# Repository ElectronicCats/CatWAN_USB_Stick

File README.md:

# CatWAN USB Stick
<p align="center">
    
</p>

<p align=center><b>Where to buy and learn more</b></p>
<p align=center>

</p>

<p align=center>
  
</p>

Are you interested in learning how LoRa works at the package level? Debugging your own LoRa hardware and trying to detect where something is wrong? Or maybe you're writing a custom application for your Internet of Things (IoT) network with LoraWAN? We have the perfect tool for you!

This CatWAN USB Stick is programmed with a special firmware image that makes it an easy-to-use LoRa sniffer. You can passively capture the data exchanges between two LoRa devices, capturing with our "LoRa Sniffer" the open-source network analysis tool that we have created to use together.

This device can work in networks LoRaWAN compatible with classes A, B, and C, although currently we do not have a firmware for this way of working, the CatWAN firmware is completely open source and you can find it in our repository along with the schematic. If you want to reprogram this device you can do it through Arduino IDE and its USB port or if you do not have to use a J-Link. ATMEL-ICE or a DIY SWD programmer

This device has a SAMD21 ARM Cortex microcontroller at 48Mhz with native USB 2.1, with 256Kb for programming, compatible with Arduino and Circuit Python.

Check our repository for more details and software downloads!

### Main characteristics

- Works with any PC, Raspberry Pi or BeagleBone, even a smartphone or tablet
- Supports packet mode LoRa® (package mode) or LoRaWAN ™ Class A, B and C
- Compatible with The Things Network and other LoRaWAN networks
- Based on the RFM95
- RX LED as reception indicator, programmable by the user
- Easy reprogramming compatible with Arduino and Circuit Python
- Compatible with the [App LoRa Sniffer](https://github.com/ElectronicCats/LoRa_Sniffer)
- Open Source

### Specifications

- Connectivity: USB 2.1
- Power Consumption: 140 ma typical TX, 20 ma idle (with power LED)
- Receiver Sensitivity: down to -146 dBm
- TX Power: adjustable up to +18.5 dBm
- Range: up to 15 km coverage in suburban and up to 5 km coverage in urban areas

### Pin connections

|Arduino |   Port    |   RFM Function|
|--------|-----------|---------------|
|0       |   PORTA4  |   DIO0   |
|1       |   PORTA23 |   DIO1   |
|2       |   PORTA27 |   DIO2   |
|13      |   PORTA14 |   LED    |
|15      |   PORTA15 |   DIO5   |
|17      |   PORTA22 |   MISO   |
|18      |   PORTA18 |   MOSI   |
|19      |   PORTA19 |   SCK    |
|20      |   PORTA17 |   SS     |

## How to contribute 
 Contributions are welcome! 

Please read the document  [**Contribution Manual**](https://github.com/ElectronicCats/electroniccats-cla/blob/main/electroniccats-contribution-manual.md)  which will show you how to contribute your changes to the project.

✨ Thanks to all our [contributors](https://github.com/ElectronicCats/CatWAN_USB_Stick/graphs/contributors)! ✨

See  [**_Electronic Cats CLA_**](https://github.com/ElectronicCats/electroniccats-cla/blob/main/electroniccats-cla.md) for more information.

See the [**community code of conduct**](https://github.com/ElectronicCats/electroniccats-cla/blob/main/electroniccats-community-code-of-conduct.md)   for a vision of the community we want to build and what we expect from it.

### Maintainer

Electronic Cats invests time and resources in providing this open-source design design, please support Electronic Cats and open-source hardware by purchasing products from Electronic Cats!

## Open Source certified.
<p align="center">
    <a href="https://www.oshwa.org/cert">
        
        <br>
        <strong>[OSHW] MX000006 | Certified open source hardware |</strong>
    </a>
</p>

Designed by Electronic Cats.

Firmware released under an GNU AGPL v3.0 license. See the LICENSE file for more information.

Hardware released under an CERN Open Hardware Licence v1.2. See the LICENSE_HARDWARE file for more information.

Electronic Cats is a registered trademark, please do not use if you sell these PCBs.

27 May 2019

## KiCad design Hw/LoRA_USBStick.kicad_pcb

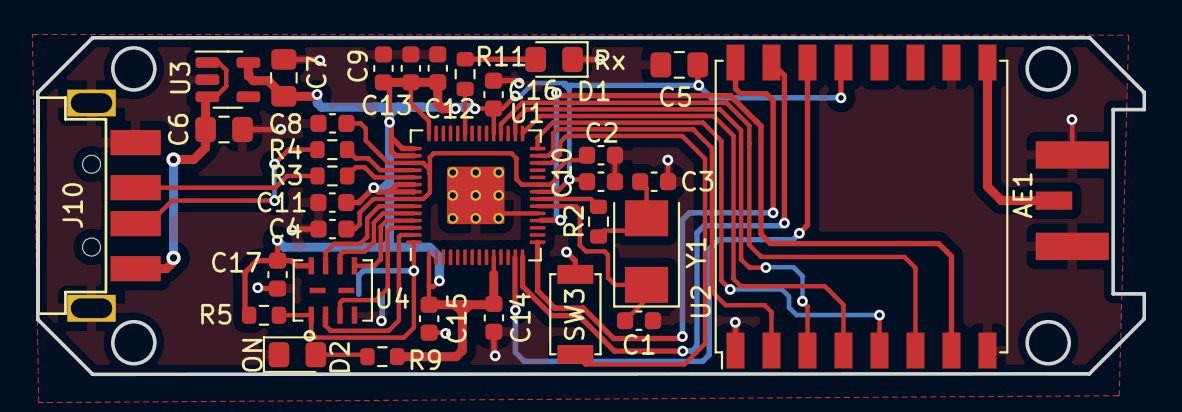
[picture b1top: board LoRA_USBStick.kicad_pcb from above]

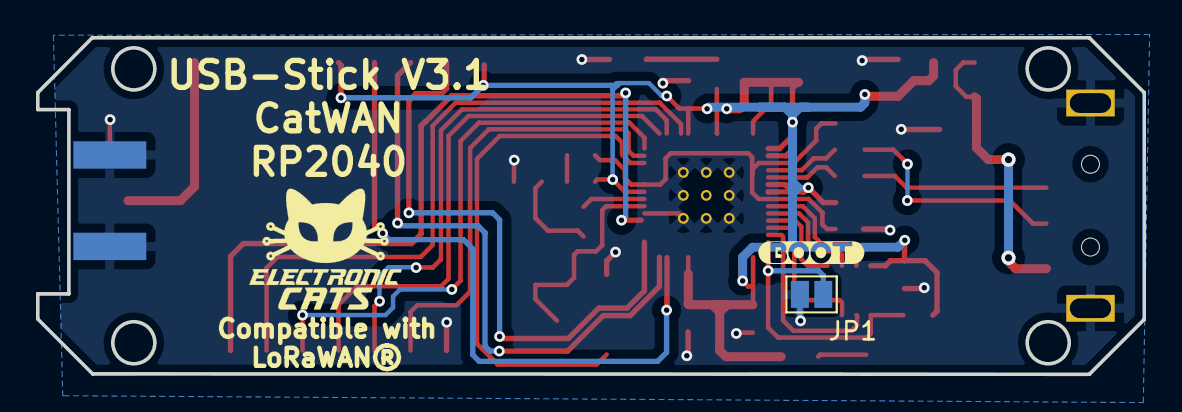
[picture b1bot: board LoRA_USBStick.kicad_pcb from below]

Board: 2 copper layers, 61.5 x 18.7 mm, 35 parts (2 on the bottom side), 31 nets.

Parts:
AE1: Antenna_Shield; SMA_EDGE
C1, C3: 27pF; C_0603_1608Metric
C2, C9: 1uF; C_0603_1608Metric
C4, C8, C10, C11, C12, C13, C14, C15, C16, C17: 0.1uF; C_0603_1608Metric
C5: 0.1uF; C_0805_2012Metric_Pad1.15x1.40mm_HandSolder
C6, C7: 10uF; C_0805_2012Metric_Pad1.15x1.40mm_HandSolder
D1: Rx; LED_0805_2012Metric_Pad1.15x1.40mm_HandSolder
D2: ON; LED_0805_2012Metric_Pad1.15x1.40mm_HandSolder
J10: USB_B; C46394
JP1: BOOT; SolderJumper-2_P1.3mm_Open_Pad1.0x1.5mm
R2: 1K; R_0603_1608Metric
R3, R4: 27; R_0603_1608Metric
R5: 10K; R_0603_1608Metric
R9, R11: 120R; R_0603_1608Metric
SW3: RST; C455281
U1: RP2040; RP2040-QFN-56
U2: RFM95W-868S2; HOPERF_RFM9XW_SMD
U3: AP2112K-3.3; SOT-23-5
U4: W25Q16JV; W25Q16JVUUIQ
Y1: 12Mhz; Crystal_SMD_5032-2Pin_5.0x3.2mm
kibuzzard-62D459CC: G***; kibuzzard-62D459CC

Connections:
+1V2: C2.1, C4.1, C8.1, U1.23 (DVDD), U1.45 (VREG_VOUT), U1.50 (DVDD)
+3V3: C5.1, C7.1, C9.1, C10.1, C11.1, C12.1, C13.1, C14.1, C15.1, C16.1, C17.1, R5.1, R9.1, U1.1 (IOVDD), U1.10 (IOVDD), U1.22 (IOVDD), U1.33 (IOVDD), U1.42 (IOVDD), U1.43 (ADC_AVDD), U1.44 (VREG_IN), U1.48 (USB_VDD), U1.49 (IOVDD), U2.13 (3_3V), U3.5 (VOUT), U4.8 (VCC)
/D+: J10.3 (D+), R3.1
/D-: J10.2 (D-), R4.1
/DIO0: U1.13 (GPIO10), U2.14 (DIO0)
/DIO1: U1.14 (GPIO11), U2.15 (DIO1)
/DIO2: U1.15 (GPIO12), U2.16 (DIO2)
/DIO5: U1.18 (GPIO15), U2.7 (DIO5)
/MISO: U1.27 (GPIO16), U2.2 (MISO)
/MOSI: U1.30 (GPIO19), U2.3 (MOSI)
/QSPI_CS: JP1.2 (B), R5.2, U1.56 (QSPI_SS), U4.1 (~CS)
/QSPI_DATA0: U1.53 (QSPI_SD0), U4.5 (DI(IO0))
/QSPI_DATA1: U1.55 (QSPI_SD1), U4.2 (DO(IO1))
/QSPI_DATA2: U1.54 (QSPI_SD2), U4.3 (IO2)
/QSPI_DATA3: U1.51 (QSPI_SD3), U4.7 (IO3)
/QSPI_SCK: U1.52 (QSPI_SCLK), U4.6 (CLK)
/RD+: R3.2, U1.47 (USB_DP)
/RD-: R4.2, U1.46 (USB_DM)
/RFM_RST: U1.32 (GPIO21), U2.6 (RESET)
/RST: SW3.1, U1.26 (RUN)
/RX_LED: R11.1, U1.37 (GPIO25)
/SCK: U1.29 (GPIO18), U2.4 (SCK)
/SS: U1.28 (GPIO17), U2.5 (NSS)
GND: AE1.2 (Shield), C1.2, C2.2, C3.2, C4.2, C5.2, C6.2, C7.2, C8.2, C9.2, C10.2, C11.2, C12.2, C13.2, C14.2, C15.2, C16.2, C17.2, D1.1 (K), D2.1 (K), J10.4 (GND), J10.5 (Shield), JP1.1 (A), SW3.2, U1.19 (TESTEN), U1.57 (GND), U2.1 (GND), U2.8 (GND@1), U2.10 (GND@2), U3.2 (GND), U4.4 (GND)
unnamed: AE1.1 (A), U2.9 (ANT)
unnamed: C1.1, U1.20 (XIN), Y1.1
unnamed: C3.1, R2.1, Y1.2
unnamed: D1.2 (A), R11.2
unnamed: D2.2 (A), R9.2
unnamed: R2.2, U1.21 (XOUT)
VBUS: C6.1, J10.1 (VBUS), U3.1 (VIN), U3.3 (EN)

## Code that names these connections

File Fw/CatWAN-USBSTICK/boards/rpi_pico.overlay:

/*
 * CatWAN USB Stick - Device Tree Overlay
 * RP2040 + RFM95W (SX1276) single-radio LoRa USB stick
 *
 * Pin mapping (from schematic):
 *   SPI0: MISO=GPIO16, CS=GPIO17, SCK=GPIO18, MOSI=GPIO19
 *   Radio: RST=GPIO21, DIO0=GPIO10, DIO1=GPIO11, DIO2=GPIO12
 *   LED: GPIO25
 */

/ {
    chosen {
        zephyr,settings-partition = &storage_partition;
    };

    aliases {
        led0 = &led_0;
        lora0 = &rfm95;
    };

    leds {
        compatible = "gpio-leds";
        led_0: led0 {
            gpios = <&gpio0 25 GPIO_ACTIVE_HIGH>;
            label = "LED";
        };
    };
};

&flash0 {
    partitions {
        /delete-node/ partition@100;

        code_partition: partition@100 {
            label = "code-partition";
            reg = <0x100 0x1eff00>;
            read-only;
        };

        storage_partition: partition@1f0000 {
            label = "storage";
            reg = <0x1f0000 0x10000>;
        };
    };
};

&zephyr_udc0 {
    cdc_acm_uart0: cdc_acm_uart0 {
        compatible = "zephyr,cdc-acm-uart";
        label = "CatWAN-LoRa";
    };

    cdc_acm_uart1: cdc_acm_uart1 {
        compatible = "zephyr,cdc-acm-uart";
        label = "CatWAN-Shell";
    };
};

&spi0 {
    status = "okay";
    pinctrl-0 = <&spi0_default>;
    pinctrl-names = "default";
    cs-gpios = <&gpio0 17 GPIO_ACTIVE_LOW>;

    rfm95: sx1276@0 {
        compatible = "semtech,sx1276";
        reg = <0>;
        spi-max-frequency = <1000000>;
        reset-gpios = <&gpio0 21 GPIO_ACTIVE_LOW>;
        dio-gpios = <&gpio0 10 GPIO_ACTIVE_HIGH>,
                    <&gpio0 11 GPIO_ACTIVE_HIGH>,
                    <&gpio0 12 GPIO_ACTIVE_HIGH>;
        power-amplifier-output = "pa-boost";
    };
};

&pinctrl {
    spi0_default: spi0_default {
        group1 {
            pinmux = <SPI0_SCK_P18>, <SPI0_TX_P19>;
        };
        group2 {
            pinmux = <SPI0_RX_P16>;
            input-enable;
        };
    };
};

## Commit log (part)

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2018-07-02 add gitignore
2018-07-02 add gitignore file
2018-07-02 add files gitignore
2018-07-02 Add project
2018-07-03 Add gerbers
2018-07-10 Add fw
2018-07-10 fix gerber
2018-07-29 Add Arduino instruction
2018-07-31 Update Bootloader to uf2
2018-08-01 Add more examples
2018-08-08 Update kicad 5
2018-08-08 add relay compatibility firmware
2018-08-21 Update measure for case
2018-09-19 remove gerbers with logo electroniccats
2018-09-19 Fix notes text
2018-10-12 Update readme to include clocksource info, Fixed a translation error in the PHY firmware.
2018-11-05 Add licenses
2018-11-06 Change USB side version 1.1v
2018-11-12 Add UID from OSHW certification
2018-11-12 Update README fix position
2018-11-25 Clean GPIO not use
2018-11-26 Remove TX and RX not used
2018-11-28 Fix vias on PCB
2018-11-29 New install instruction for SAMD Core Electronic Cats
2019-01-08 Add v2.0
2019-02-12 Add ping pong example
2019-03-27 Add forlder for phy examples
2019-03-27 Add LoRaWAN examples with two libraries
2019-03-27 Move phy examples
2019-03-27 Add readme for examples
2019-03-27 Add readme on examples
2019-03-27 Update PHY README
2019-04-05 erase v0.0.1 sniffer fw
2019-04-05 Add new loraSniffer
2019-04-07 add DIO5 support fix functions
2019-05-27 add pin table
2019-05-27 Fix pin table
2019-05-28 Fix traces v2.3
2019-10-30 update bootloader and VID
2020-01-09 Update version
2020-01-09 hide cupper zones
2020-02-04 Update LoRaSniffer CLI
2020-02-25 Update relay stick
2020-07-01 add datasheet
2020-08-03 fix enable LDO
2020-08-03 Fix layout on enable LDO
2020-09-13 udpate version with u.fl connector
2020-10-15 fix part number micro
2022-06-23 update set_tx, set_tx_ascii, set_chann
2022-06-24 Replace the ATSAMD21E with RP2040
2022-06-24 Assigned footprints
2022-06-28 Change labels, assigned and check the footprints
2022-06-28 change labels for memory and RX_LED
2022-06-28 remove duplicate tags, I2C and UART
2022-06-28 change button for jumper force jumper
2022-06-29 Place footprints on the PCB
2022-06-30 add footprint memory flash
2022-06-30 update set_tx, add set_tx_hex
2022-07-01 New floor plan
2022-07-06 PCB route
2022-07-06 update floorplan and routing
2022-07-07 Change a fototprint and routing
2022-07-11 fix routing
2022-08-09 Add labels
2022-08-09 update labels
2022-08-15 add set/get codig rate
2022-08-16 update hex format in serial prints
2022-08-18 update set_tx, set_tx_hex to send a series of bytes
2022-08-19 unnecessary comments were removed
2022-08-23 Update README.md
    wiki and getting started link added
2023-01-09 add set_sw, set_pl, set_tp and respective gets
2023-03-15 Add LoRaReceiver
2023-12-05 Updated images and links
    The CatWAN USB Stick image was added, the open-source certified image and link were improved, and the board purchase link was added.
2023-12-07 Information update
    The information was organized
2023-12-07 Added link to CatWAN image
    The CatWAN image redirects you to the wiki
2023-12-13 Update lorawan-send-class-A.ino
    Updated code to make it work with the latest Beelan-LoRaWAN library release
2023-12-29 Format Updated
    The readme format has been updated
2024-01-03 cmd set_inv_iq added
2024-01-16 Remove restriction of frequency, change set_tx name functions
2024-02-12 BOM updated
2024-02-19 commented lines were removed
2024-03-20 fix(Hw) Measurements in margen layer changed to user drawings
2024-03-20 feat(Hw) Update version
2024-04-09 Update README.md
    How to contribute added
2024-04-10 feat (docs): Update README.md
2024-04-24 feat(docs): add distributor button
2024-04-24 feat(docs): add text and distributor button
2024-10-02 feat (fw): Update LoRaSniffer.ino
2024-10-14 feat (fw): Update LoRaSniffer.ino
    added command to enable or disbale ecryption
2024-10-14 feat(fw): adjust min/max frequency for RFM95W module
2024-10-14 feat: stop simulation sensor
2024-10-15 docs: add library links
2025-03-11 fix: change name folder for bootloader SAMD21
2025-03-11 docs: remove datasheet samd21
2025-03-11 Update examples
2025-03-14 fix: restore functions that were previously removed
2025-03-14 chore: pre-commit passed
2025-03-19 chore: reference to the crypto library was added
2025-06-04 feat(pins): to define radio module pins
    To define radio module pins for supporting non-official cores (arduino-pico)
2025-06-04 fix: RFM_DIO0
    To change pin number for RFM_DIO0
2026-04-10 Add zephyr firmware, modify gitignore
